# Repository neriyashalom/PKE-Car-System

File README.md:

# PKE-Car-System

# ESP32-S3 Based PKE System for Vehicle Access and Ignition

## Project Overview
This project presents the design and implementation of a Passive Keyless Entry (PKE) system for a vehicle, based on the ESP32-S3 microcontroller.  
The system enables keyless door locking and unlocking, mirror folding and unfolding, and vehicle ignition control through a Start-Stop push button, using BLE proximity detection.

The project combines hardware, firmware, PCB design, and practical testing into a complete embedded automotive-oriented solution.  
A dedicated PCB was designed to integrate the ESP32-S3 controller, protection circuits, input conditioning stages, relay drivers, and relay blocks required for interfacing with the vehicle.

In addition to the PKE functionality, the system was designed to operate alongside the original vehicle key without interfering with its normal operation.

## System Architecture
The system is built around the following main blocks:

- ESP32-S3 controller
- BLE-based proximity detection
- Start-Stop push button interface
- Vehicle input conditioning circuits
- Protection and voltage level adaptation circuits
- Relay drivers and relay blocks
- Dedicated custom PCB
- Power management and DC-DC conversion

## Main Inputs
- BLE tag for proximity detection
- Brake pedal signal
- Handbrake signal
- Door status signal
- Ignition status signal
- Start-Stop button feedback

## Main Outputs
- Door lock control
- Door unlock control
- Mirror fold and unfold control
- ACC control
- IGN control
- START control
- Turn signal indication outputs
- Start-Stop button LED control

## Key Features
- Passive keyless vehicle access using BLE proximity detection
- Start-Stop ignition control based on defined safety conditions
- Support for vehicle functions such as mirrors, blinkers, and ignition lines
- Dedicated PCB for structured and reliable hardware integration
- State-based firmware logic for clear and predictable system behavior
- Practical implementation and testing on prototype and final PCB
- Compatibility with the original vehicle key system

## Repository Structure
- `Code/` - source code for the ESP32-S3 based PKE controller
- `KICAD/` - schematic and PCB design files created in KiCad
- `Multisim/` - simulation files used during the design and verification stages
- `ESP32S3.jpg` - image of the implemented ESP32-S3 based hardware
- `Final Project.pdf` - final project documentation and report
- `README.md` - general description of the project and repository contents

## Tools and Technologies
- **Microcontroller:** ESP32-S3
- **Firmware:** Arduino IDE, C/C++
- **PCB Design:** KiCad
- **Simulation:** Multisim
- **Communication:** BLE
- **Hardware:** Relay drivers, relays, protection circuits, DC-DC converter
- **Application Domain:** Embedded systems, automotive electronics

## Project Outcome
The project demonstrates a complete embedded hardware-software solution for implementing a custom PKE system in a vehicle environment.  
It includes concept definition, hardware design, PCB implementation, firmware development, simulation, prototype testing, and final integration.

## Author
Final project in Electrical and Electronics Engineering  
Developer: Neriya Shalom

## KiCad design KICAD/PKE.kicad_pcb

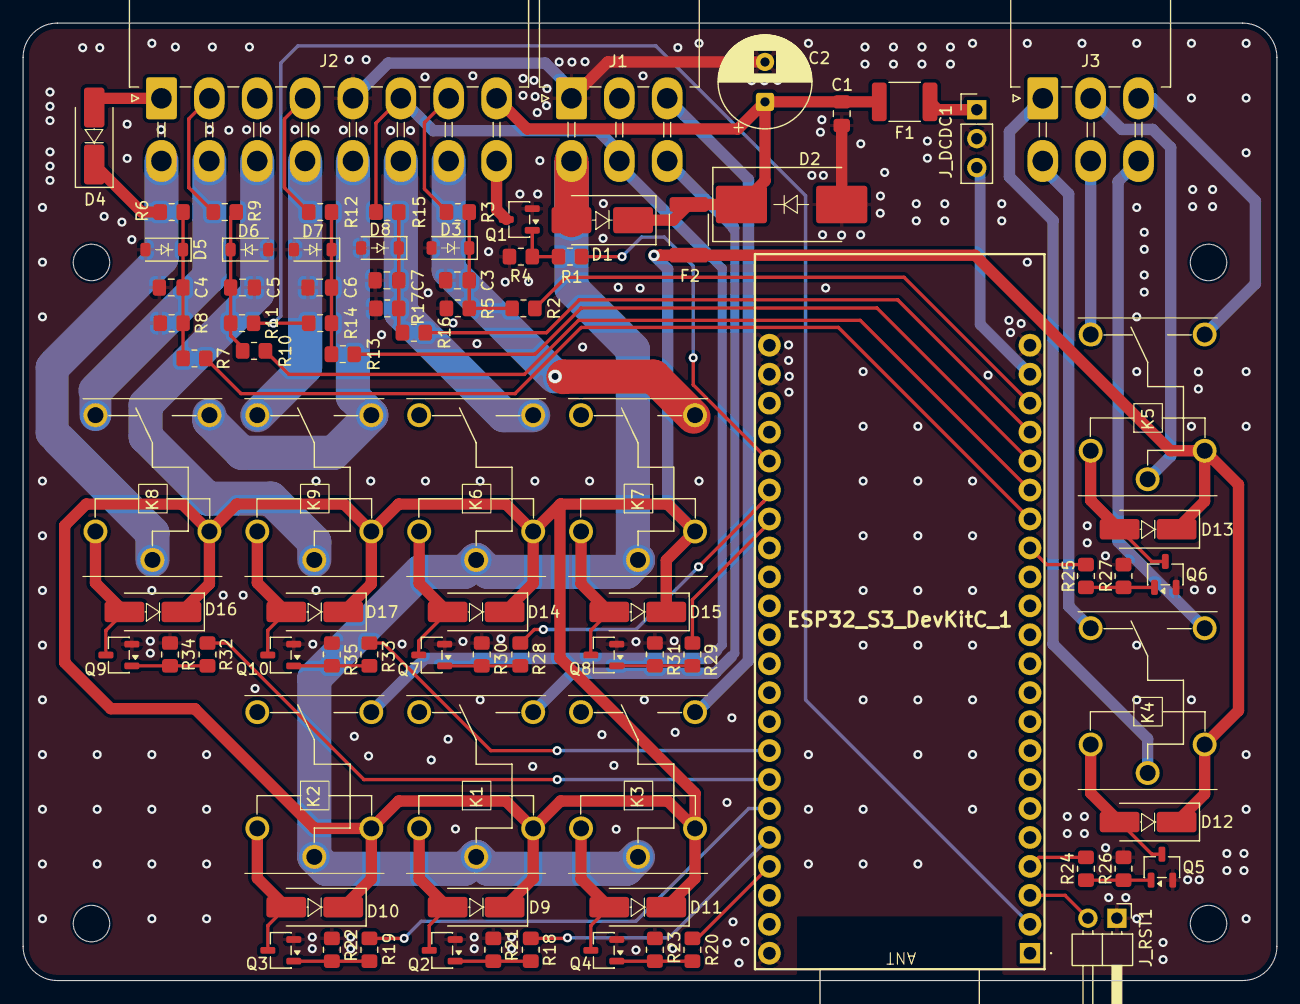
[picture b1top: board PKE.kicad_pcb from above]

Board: 2 copper layers, 110.0 x 84.0 mm, 90 parts (0 on the bottom side), 69 nets.

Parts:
C1, C3, C4, C5, C6, C7: 100n; C_0805_2012Metric_Pad1.18x1.45mm_HandSolder
C2: 50V220u; CP_Radial_D8.0mm_P3.50mm
D1: SR560; D_SMB_Handsoldering
D2: P6KE18A; D_SMC_Handsoldering
D3, D5, D6, D7, D8: 1N4728A; D_SOD-123
D4, D9, D10, D11, D12, D13, D14, D15, D16, D17: 1N4007; D_SMA_Handsoldering
ESP32_S3_DevKitC_1: ESP32_S3_DevKitC; ESP32S3DevKitC1N32R16V
F1: FUSE_DCDC 1.1A; Fuse_1812_4532Metric_Pad1.30x3.40mm_HandSolder
F2: FUSE_COILS 1.1A; Fuse_1812_4532Metric_Pad1.30x3.40mm_HandSolder
H1, H2, H3, H4: MountingHole; MountingHole_3.2mm_M3
J1, J3: Conn_01x06; Molex_Mini-Fit_Jr_5569-06A2_2x03_P4.20mm_Horizontal
J2: Conn_01x14; Molex_Mini-Fit_Jr_5569-16A2_2x08_P4.20mm_Horizontal
J_DCDC1: Conn_01x03; PinHeader_1x03_P2.54mm_Vertical
J_RST1: Conn_01x02; PinHeader_1x02_P2.54mm_Horizontal
K1, K2, K3, K4, K5, K6, K7, K8, K9: CMA51H-S-DC12V-C; CMA51HSDC12VC
Q1, Q2, Q3, Q4, Q5, Q6, Q7, Q8, Q9, Q10: 2N2222A; SOT-23-3
R1, R2, R7, R10, R13, R16, R18, R19, R20, R24, R25, R28, R29, R32, R33: 1k; R_0805_2012Metric_Pad1.20x1.40mm_HandSolder
R3, R6, R15: 30k; R_0805_2012Metric_Pad1.20x1.40mm_HandSolder
R4, R21, R22, R23, R26, R27, R30, R31, R34, R35: 100k; R_0805_2012Metric_Pad1.20x1.40mm_HandSolder
R5, R8, R17: 10k; R_0805_2012Metric_Pad1.20x1.40mm_HandSolder
R9, R12: 4.7k; R_0805_2012Metric_Pad1.20x1.40mm_HandSolder
R11, R14: 47k; R_0805_2012Metric_Pad1.20x1.40mm_HandSolder

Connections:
3V3: ESP32_S3_DevKitC_1.2 (3V3_2), R11.1, R14.1
+5V: ESP32_S3_DevKitC_1.21 (5V), J_DCDC1.3
+12V_COILS: D9.1 (K), D10.1 (K), D11.1 (K), D12.1 (K), D13.1 (K), D14.1 (K), D15.1 (K), D16.1 (K), D17.1 (K), F2.1, K1.3 (COIL_2), K2.3 (COIL_2), K3.3 (COIL_2), K4.3 (COIL_2), K5.3 (COIL_2), K6.3 (COIL_2), K7.3 (COIL_2), K8.3 (COIL_2), K9.3 (COIL_2)
+12V_ELEC: C1.2, C2.1, D1.1 (K), D2.1 (K), F1.2, F2.2, J2.8
+12V_MIRROR_IN: J2.13, K8.5 (NO), K9.5 (NO)
+12V_RAW: D1.2 (A), J1.4, K1.2 (COM), K2.2 (COM), K3.2 (COM), K6.2 (COM), K7.2 (COM)
ACC: ESP32_S3_DevKitC_1.27 (2), R18.2
ACC_OUT: J1.6, K1.5 (NO)
BRAKE_12V: D4.1 (K), R6.1
BRAKE_SIG: ESP32_S3_DevKitC_1.16 (10), R7.1
BTN_GND: J2.16, Q1.3 (C)
BTN_LED: ESP32_S3_DevKitC_1.40 (21), R1.2
BTN_SIG: ESP32_S3_DevKitC_1.20 (14), R2.2
BTN_TRIG: J2.7, R3.2
DOOR_NEG: J2.4, R12.1
DOOR_SIG: ESP32_S3_DevKitC_1.18 (12), R13.1
GND: C1.1, C2.2, C3.1, C4.1, C5.1, C6.1, C7.1, D2.2 (A), D3.2 (A), D5.2 (A), D6.2 (A), D7.2 (A), D8.2 (A), ESP32_S3_DevKitC_1.22 (G_1), ESP32_S3_DevKitC_1.23 (G_2), ESP32_S3_DevKitC_1.43 (G_3), ESP32_S3_DevKitC_1.44 (G_4), J1.1, J2.5, J_DCDC1.2, J_RST1.1, Q1.2 (E), Q2.2 (E), Q3.2 (E), Q4.2 (E), Q5.2 (E), Q6.2 (E), Q7.2 (E), Q8.2 (E), Q9.2 (E), Q10.2 (E), R4.2, R5.1, R8.1, R17.1, R21.2, R22.2, R23.2, R26.2, R27.2, R30.2, R31.2, R34.2, R35.2
HB_NEG: J2.2, R9.1
HB_SIG: ESP32_S3_DevKitC_1.17 (11), R10.1
IGN: ESP32_S3_DevKitC_1.28 (42), R19.2
IGN_OUT: J1.5, J2.6, K2.5 (NO), R15.1
IGN_SIG: ESP32_S3_DevKitC_1.19 (13), R16.1
LOCK: ESP32_S3_DevKitC_1.4, R24.2
LOCK_COM: J3.1, K4.2 (COM)
LOCK_NC: J3.4, K4.4 (NC)
LOCK_NO: J3.6, K4.5 (NO)
L_BLINK: ESP32_S3_DevKitC_1.38 (48), R29.2
L_BLINK_OUT: J2.15, K7.5 (NO)
MIRROR_CLOSE: ESP32_S3_DevKitC_1.29 (41), R32.2
MIRROR_CLOSE_MOTOR: J2.9, K8.2 (COM)
MIRROR_CLOSE_SW: J2.10, K8.4 (NC)
MIRROR_OPEN: ESP32_S3_DevKitC_1.30 (40), R33.2
MIRROR_OPEN_MOTOR: J2.11, K9.2 (COM)
MIRROR_OPEN_SW: J2.12, K9.4 (NC)
unnamed: C3.2, D3.1 (K), R2.1, R3.1, R5.2
unnamed: D4.2 (A), J2.1
unnamed: C4.2, D5.1 (K), R6.2, R7.2, R8.2
unnamed: C5.2, D6.1 (K), R9.2, R10.2, R11.2
unnamed: C6.2, D7.1 (K), R12.2, R13.2, R14.2
unnamed: C7.2, D8.1 (K), R15.2, R16.2, R17.2
unnamed: D9.2 (A), K1.1 (COIL_1), Q2.3 (C)
unnamed: D10.2 (A), K2.1 (COIL_1), Q3.3 (C)
unnamed: D11.2 (A), K3.1 (COIL_1), Q4.3 (C)
unnamed: D12.2 (A), K4.1 (COIL_1), Q5.3 (C)
unnamed: D13.2 (A), K5.1 (COIL_1), Q6.3 (C)
unnamed: D14.2 (A), K6.1 (COIL_1), Q7.3 (C)
unnamed: D15.2 (A), K7.1 (COIL_1), Q8.3 (C)
unnamed: D16.2 (A), K8.1 (COIL_1), Q9.3 (C)
unnamed: D17.2 (A), K9.1 (COIL_1), Q10.3 (C)
unnamed: F1.1, J_DCDC1.1
unnamed: Q1.1 (B), R1.1, R4.1
unnamed: Q2.1 (B), R18.1, R21.1
unnamed: Q3.1 (B), R19.1, R22.1
unnamed: Q4.1 (B), R20.1, R23.1
unnamed: Q5.1 (B), R24.1, R26.1
unnamed: Q6.1 (B), R25.1, R27.1
unnamed: Q7.1 (B), R28.1, R30.1
unnamed: Q8.1 (B), R29.1, R31.1
unnamed: Q9.1 (B), R32.1, R34.1
unnamed: Q10.1 (B), R33.1, R35.1
RST: ESP32_S3_DevKitC_1.3 (RST), J_RST1.2
R_BLINK: ESP32_S3_DevKitC_1.39 (47), R28.2
R_BLINK_OUT: J2.14, K6.5 (NO)
START: ESP32_S3_DevKitC_1.26 (1), R20.2
START_OUT: J1.3, K3.5 (NO)
UNLOCK: ESP32_S3_DevKitC_1.15 (9), R25.2
UNLOCK_COM: J3.2, K5.2 (COM)
UNLOCK_NC: J3.5, K5.4 (NC)
UNLOCK_NO: J3.3, K5.5 (NO)

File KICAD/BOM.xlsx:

Reference | Footprint | Qty | Perfboard (ללוח הלחמה לבדיקה) | SMD (ללוח PCB מודפס)
C1,C3,C4,C5,C6,C7 | Capacitor_SMD:C_0805_2012Metric_Pad1.18x1.45mm_HandSolder | 6 | 100n THT | Capacitor 100nF 50V X7R 0805
C2 | Capacitor_THT:CP_Radial_D8.0mm_P3.50mm | 1 | 50V220u THT | Electrolytic Capacitor 220uF 50V Radial_D8.0mm_P3.50mm
D1 | Diode_SMD:D_SMB_Handsoldering | 1 | SR560 THT | SS56 SMB
D2 | Diode_SMD:D_SMC_Handsoldering | 1 | P6KE18A THT | SMCJ18A SMC
D3,D5,D6,D7,D8 | Diode_SMD:D_SOD-123 | 5 | 1N4728A THT | BZT52C3V3 SOD-123
D4,D9,D10,D11,D12,D13,D14,D15,D16,D17 | Diode_SMD:D_SMA_Handsoldering | 10 | 1N4007 THT | 1N4007 SMA
ESP32_S3_DevKitC_1 | ESP32-S3-DevKitC-1-N32R16V:ESP32S3DevKitC1N32R16V | 1 | ESP32_S3_DevKitC THT | ESP32_S3_DevKitC THT
F1 | Fuse:Fuse_1812_4532Metric_Pad1.30x3.40mm_HandSolder | 1 | FUSE_DCDC 1.1A THT | 1812 4.8*3.2mm
F2 | Fuse:Fuse_1812_4532Metric_Pad1.30x3.40mm_HandSolder | 1 | FUSE_COILS 1.1A THT | 1812 4.8*3.2mm
J1,J3 | Connector_Molex:Molex_Mini-Fit_Jr_5569-06A2_2x03_P4.20mm_Horizontal | 2 | Molex_Mini-Fit_Jr_5569-06A2_2x03 THT | Molex_Mini-Fit_Jr_5569-06A2_2x03 THT
J2 | Connector_Molex:Molex_Mini-Fit_Jr_5569-16A2_2x08_P4.20mm_Horizontal | 1 | Molex_Mini-Fit_Jr_5569-16A2_2x08 THT | Molex_Mini-Fit_Jr_5569-16A2_2x08 THT
J_DCDC1 | Connector_PinHeader_2.54mm:PinHeader_1x03_P2.54mm_Vertical | 1 | 3 Holes for external module THT | 3 Holes for external module THT
J_RST1 | Connector_PinHeader_2.54mm:PinHeader_1x02_P2.54mm_Horizontal | 1 | 2 Holes for external module THT | 2 Holes for external module THT
K1,K2,K3,K4,K5,K6,K7,K8,K9 | CMA51H_RELAY:CMA51HSDC12VC | 9 | CMA51H-S-DC12V-C THT | CMA51H-S-DC12V-C THT
Q1,Q2,Q3,Q4,Q5,Q6,Q7,Q8,Q9,Q10 | Package_TO_SOT_SMD:SOT-23-3 | 10 | 2N2222A THT | MMBT2222A SOT-23-3
R1,R2,R7,R10,R13,R16,R18,R19,R20,R24,R25,R28,R29,R32,R33 | Resistor_SMD:R_0805_2012Metric_Pad1.20x1.40mm_HandSolder | 15 | 1k THT | Resistor 1k 0805
R3,R6,R15 | Resistor_SMD:R_0805_2012Metric_Pad1.20x1.40mm_HandSolder | 3 | 30k THT | Resistor 30k 0805
R4,R21,R22,R23,R26,R27,R30,R31,R34,R35 | Resistor_SMD:R_0805_2012Metric_Pad1.20x1.40mm_HandSolder | 10 | 100k THT | Resistor 100k 0805
R5,R8,R17 | Resistor_SMD:R_0805_2012Metric_Pad1.20x1.40mm_HandSolder | 3 | 10k THT | Resistor 10k 0805
R9,R12 | Resistor_SMD:R_0805_2012Metric_Pad1.20x1.40mm_HandSolder | 2 | 4.7k THT | Resistor 4.7k 0805
R11,R14 | Resistor_SMD:R_0805_2012Metric_Pad1.20x1.40mm_HandSolder | 2 | 47k THT | Resistor 47k 0805

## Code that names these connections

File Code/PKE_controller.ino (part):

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// ==========================================
// 2. הגדרת פינים (GPIO מדויק)
// ==========================================
const int PIN_BRAKE_SIG    = 10;
const int PIN_HB_SIG       = 11;
const int PIN_DOOR_SIG     = 12;
const int PIN_IGN_SIG      = 13;
const int PIN_BTN_SIG      = 14;

const int PIN_LOCK         = 4;
const int PIN_UNLOCK       = 9;
const int PIN_START        = 1;
const int PIN_ACC          = 2;
const int PIN_IGN          = 42;
const int PIN_MIRROR_CLOSE = 41;
const int PIN_MIRROR_OPEN  = 40;
const int PIN_L_BLINK      = 48;
const int PIN_R_BLINK      = 47;
const int PIN_BTN_LED      = 21;

// ==========================================
// 3. ערכי זמן קבועים
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void setRelay(int pin, bool state) {
  if (digitalRead(pin) != state) {
    digitalWrite(pin, state ? HIGH : LOW);
    if (pin == PIN_IGN) {
      espControlsIgnition = state;
      if (!state) {
        ignReleasedByEspTime = millis();
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}

void readAllInputs() {
  debounceInput(PIN_BRAKE_SIG, brakeState, brakePressed,      true);
  debounceInput(PIN_HB_SIG,    hbState,    hbPulled,          false); // טריגר שלילי
  debounceInput(PIN_DOOR_SIG,  doorState,  isDoorOpen,        true);
  debounceInput(PIN_IGN_SIG,   ignState,   originalIgnActive, true);
  debounceInput(PIN_BTN_SIG,   btnState,   btnPressed,        true);
}

// סימולציה דרך Serial לבדיקות ללא חומרה
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  currentBlinkOnTime    = UNLOCK_BLINK_ON_TIME;
  currentBlinkOffTime   = UNLOCK_BLINK_OFF_TIME;
  blinkerLastToggleTime = millis();
  setRelay(PIN_L_BLINK, true); setRelay(PIN_R_BLINK, true);
}

// FR-12 (תרחיש 16): UNLOCK בלבד ליישור פיזי — ללא מראות וללא הבהובים
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  isMirrorClosing = true; mirrorActionStartTime = millis();
  isBlinking = true; isSolidBlink = true;
  blinkerLastToggleTime = millis();
  setRelay(PIN_L_BLINK, true); setRelay(PIN_R_BLINK, true);
}

void triggerLockFailureBlinks() {
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  currentBlinkOnTime    = LOCK_FAIL_BLINK_ON_TIME;
  currentBlinkOffTime   = LOCK_FAIL_BLINK_OFF_TIME;
  blinkerLastToggleTime = millis();
  setRelay(PIN_L_BLINK, true); setRelay(PIN_R_BLINK, true);
}

// FR-10, FR-11: כישלון נעילה — LOCK פולס ואז UNLOCK פולס + 5 הבהובים
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  isLockFailSequence = true;
  lockFailStep       = 1;
  lockFailTimer      = millis();
  setRelay(PIN_LOCK, true);
  // ללא isMirrorClosing — FR-10: בכישלון נעילה מראות לא זזות
}

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  isLockFailSequence = false;
  lockFailStep       = 0;
  lockFailNotified   = false;
  setRelay(PIN_LOCK,   false);
  setRelay(PIN_UNLOCK, false);

  isMirrorOpening = false;
  isMirrorClosing = false;
  setRelay(PIN_MIRROR_OPEN,  false);
  setRelay(PIN_MIRROR_CLOSE, false);

  isBlinking = false;
  setRelay(PIN_L_BLINK, false);
  setRelay(PIN_R_BLINK, false);
}

// ביטול רצף כישלון נעילה — עוצר את כל ה-PKE
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  currentLedOnTime    = LED_BLINK_ON_TIME;
  currentLedOffTime   = LED_BLINK_OFF_TIME;
  btnLedLastToggle    = millis();
  setRelay(PIN_BTN_LED, !btnLedBaseState);
}

void triggerLedError() {
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  currentLedOnTime    = LED_ERROR_BLINK_ON_TIME;
  currentLedOffTime   = LED_ERROR_BLINK_OFF_TIME;
  btnLedLastToggle    = millis();
  setRelay(PIN_BTN_LED, true);
}

// --- מנהל פלטים Non-blocking — SW-04 ---
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  // רצף כישלון נעילה: LOCK pulse → UNLOCK pulse → 5 הבהובים — FR-10, FR-11
  if (isLockFailSequence) {
    if (lockFailStep == 1 && (currentMillis - lockFailTimer >= LOCK_PULSE)) {
      setRelay(PIN_LOCK, false);
      lockFailStep = 2;
      setRelay(PIN_UNLOCK, true);
      lockFailTimer = currentMillis;
    }
    else if (lockFailStep == 2 && (currentMillis - lockFailTimer >= UNLOCK_PULSE)) {
      setRelay(PIN_UNLOCK, false);
      triggerLockFailureBlinks();
      isLockFailSequence = false;
      lockFailStep       = 0;
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  }

  if (isUnlocking && !isLockFailSequence) {
    setRelay(PIN_UNLOCK, true);
    if (currentMillis - lockActionStartTime >= UNLOCK_PULSE) {
      setRelay(PIN_UNLOCK, false);
      isUnlocking = false;
    }
  }
  if (isLocking && !isLockFailSequence) {
    setRelay(PIN_LOCK, true);
    if (currentMillis - lockActionStartTime >= LOCK_PULSE) {
      setRelay(PIN_LOCK, false);
      isLocking = false;
    }
  }

  if (isMirrorOpening) {
    setRelay(PIN_MIRROR_OPEN, true);
    if (currentMillis - mirrorActionStartTime >= MIRROR_OPEN_PULSE) {
      setRelay(PIN_MIRROR_OPEN, false);
      isMirrorOpening = false;
    }
  }
  if (isMirrorClosing) {
    setRelay(PIN_MIRROR_CLOSE, true);
    if (currentMillis - mirrorActionStartTime >= MIRROR_CLOSE_PULSE) {
      setRelay(PIN_MIRROR_CLOSE, false);
      isMirrorClosing = false;
    }
  }
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    if (isSolidBlink) {
      // נעילה: וינקרים דולקים רציף 3 שניות — FR-07
      if (currentMillis - blinkerLastToggleTime >= LOCK_BLINK_DURATION) {
        setRelay(PIN_L_BLINK, false); setRelay(PIN_R_BLINK, false);
        isBlinking = false;
      }
    } else {
      // פתיחה / שגיאת נעילה: הבהובים ספורים — FR-06, FR-11
      bool isOn = digitalRead(PIN_L_BLINK);
      unsigned long waitTime = isOn ? currentBlinkOnTime : currentBlinkOffTime;
      if (currentMillis - blinkerLastToggleTime >= waitTime) {
        blinkerToggleCount++;
        if (blinkerToggleCount >= blinkerTargetToggles) {
          setRelay(PIN_L_BLINK, false); setRelay(PIN_R_BLINK, false);
          isBlinking = false;
        } else {
          setRelay(PIN_L_BLINK, !isOn); setRelay(PIN_R_BLINK, !isOn);
          blinkerLastToggleTime = currentMillis;
        }
      }
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  }

  if (isBtnLedBlinking) {
    bool isOn = digitalRead(PIN_BTN_LED);
    unsigned long waitTime = isOn ? currentLedOnTime : currentLedOffTime;
    if (currentMillis - btnLedLastToggle >= waitTime) {
      btnLedToggleCount++;
      if (btnLedToggleCount >= btnLedTargetToggles) {
        isBtnLedBlinking = false;
        setRelay(PIN_BTN_LED, btnLedBaseState); // חזרה למצב בסיס
      } else {
        setRelay(PIN_BTN_LED, !isOn);
        btnLedLastToggle = currentMillis;
      }
    }
  } else {
    setRelay(PIN_BTN_LED, btnLedBaseState);
  }
}

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void setup() {
  Serial.begin(115200);

  pinMode(PIN_BRAKE_SIG, INPUT);
  pinMode(PIN_HB_SIG,    INPUT);
  pinMode(PIN_DOOR_SIG,  INPUT);
  pinMode(PIN_IGN_SIG,   INPUT);
  pinMode(PIN_BTN_SIG,   INPUT);

  int outputs[] = {PIN_LOCK, PIN_UNLOCK, PIN_START, PIN_ACC, PIN_IGN,
                   PIN_MIRROR_CLOSE, PIN_MIRROR_OPEN, PIN_L_BLINK, PIN_R_BLINK, PIN_BTN_LED};
  for (int i = 0; i < 10; i++) {
    pinMode(outputs[i], OUTPUT);
    digitalWrite(outputs[i], LOW); // SR-08: כל הפלטים בטוחים באתחול
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    // STATE_IDLE: מצב מעבר רגעי — FR-37, SR-08
    // מאפס פלטים ומנתב מיד ל-LOCKED או UNLOCKED, אינו מצב שהייה
    case STATE_IDLE:
      setRelay(PIN_ACC,   false);
      setRelay(PIN_IGN,   false);
      setRelay(PIN_START, false);
      if (isKeyPresent) {
        triggerUnlockSequence();
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
    // STATE_LOCKED: אין מפתח, רכב נעול
    case STATE_LOCKED:
      setRelay(PIN_ACC,   false);
      setRelay(PIN_IGN,   false);
      setRelay(PIN_START, false);
      if (isKeyPresent) {
        // SR-12: מבטל פולס LOCK שעלול עדיין לרוץ לפני פתיחה
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    // STATE_UNLOCKED: רכב פתוח וכבוי, ממתין לפעולת משתמש או להחלטת PKE
    // (אפשר להיות כאן גם ללא מפתח — אחרי אובדן מפתח, אחרי כישלון נעילה, אחרי כיבוי)
    case STATE_UNLOCKED:
      setRelay(PIN_ACC,   false);
      setRelay(PIN_IGN,   false);
      setRelay(PIN_START, false);

      // ניהול רצף כישלון נעילה פעיל — SW-05, FR-12 (תרחיש 16)
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
    // STATE_ACC_ON: ACC פעיל, IGN כבוי
    case STATE_ACC_ON:
      setRelay(PIN_ACC, true);

      // FR-35: כיבוי אוטומטי אחרי 5 דקות ללא מפתח
      if (!isKeyPresent && keyLostStartTime > 0 &&
          (millis() - keyLostStartTime > ACC_IGN_AUTO_OFF_TIMEOUT)) {
        setRelay(PIN_ACC, false);
        ledSuppressedAfterShutdown = true;
        changeState(STATE_UNLOCKED);
        break;
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        } else {
          // FR-32: כיבוי מ-ACC ללא ברקס מותר כשהמנוע לא פועל (גם אחרי אובדן מפתח)
          triggerLedFeedback();
          setRelay(PIN_ACC, false);
          ledSuppressedAfterShutdown = true;
          changeState(STATE_UNLOCKED);
        }
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
    // STATE_IGN_ON: ACC + IGN פעילים, מנוע לא פועל
    case STATE_IGN_ON:
      setRelay(PIN_ACC, true);
      setRelay(PIN_IGN, true);

      // FR-35: כיבוי אוטומטי אחרי 5 דקות ללא מפתח
      if (!isKeyPresent && keyLostStartTime > 0 &&
          (millis() - keyLostStartTime > ACC_IGN_AUTO_OFF_TIMEOUT)) {
        setRelay(PIN_ACC, false);
        setRelay(PIN_IGN, false);
        ledSuppressedAfterShutdown = true;
        changeState(STATE_UNLOCKED);
        break;
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        } else {
          // FR-32: כיבוי — תנאי התנעה לא מתקיימים במלואם (כולל אובדן מפתח)
          triggerLedFeedback();
          setRelay(PIN_ACC, false);
          setRelay(PIN_IGN, false);
          ledSuppressedAfterShutdown = true;
          changeState(STATE_UNLOCKED);
        }
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        // FR-17, FR-18: תמיד 1s לפני START — לא משנה מאיפה הגענו
        if (millis() - stateEnterTime < PRE_START_DELAY) {
          // שלב 1: ACC + IGN, ממתינים לייצוב ולחץ דלק
          setRelay(PIN_ACC,   true);
          setRelay(PIN_IGN,   true);
          setRelay(PIN_START, false);
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
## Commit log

2026-03-25 Initial project upload
